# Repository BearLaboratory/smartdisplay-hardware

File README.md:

<h1 align="center" style="font-size:50px;font-weight:bold">SmartDisplay-Hardware</h1>
<p align="center">墨水屏个人显示终端硬件</p>
<p align="center">

</p>

## 描述

smartdisplay硬件基于ESP32及2.9寸墨水屏，拥有WiFi及蓝牙BLE功能。

可通过WiFi连接网络请求相关数据，同时可以通过蓝牙控制系统。

## 硬件设计

## BUG

+ 充电芯片TP4054充电功率过小
> 充电功率TP4054只有500ma,导致边冲边放无法更好给电池充电。

+ 无时钟芯片
> 无时钟芯片导致时间不准确

## 固件及APP

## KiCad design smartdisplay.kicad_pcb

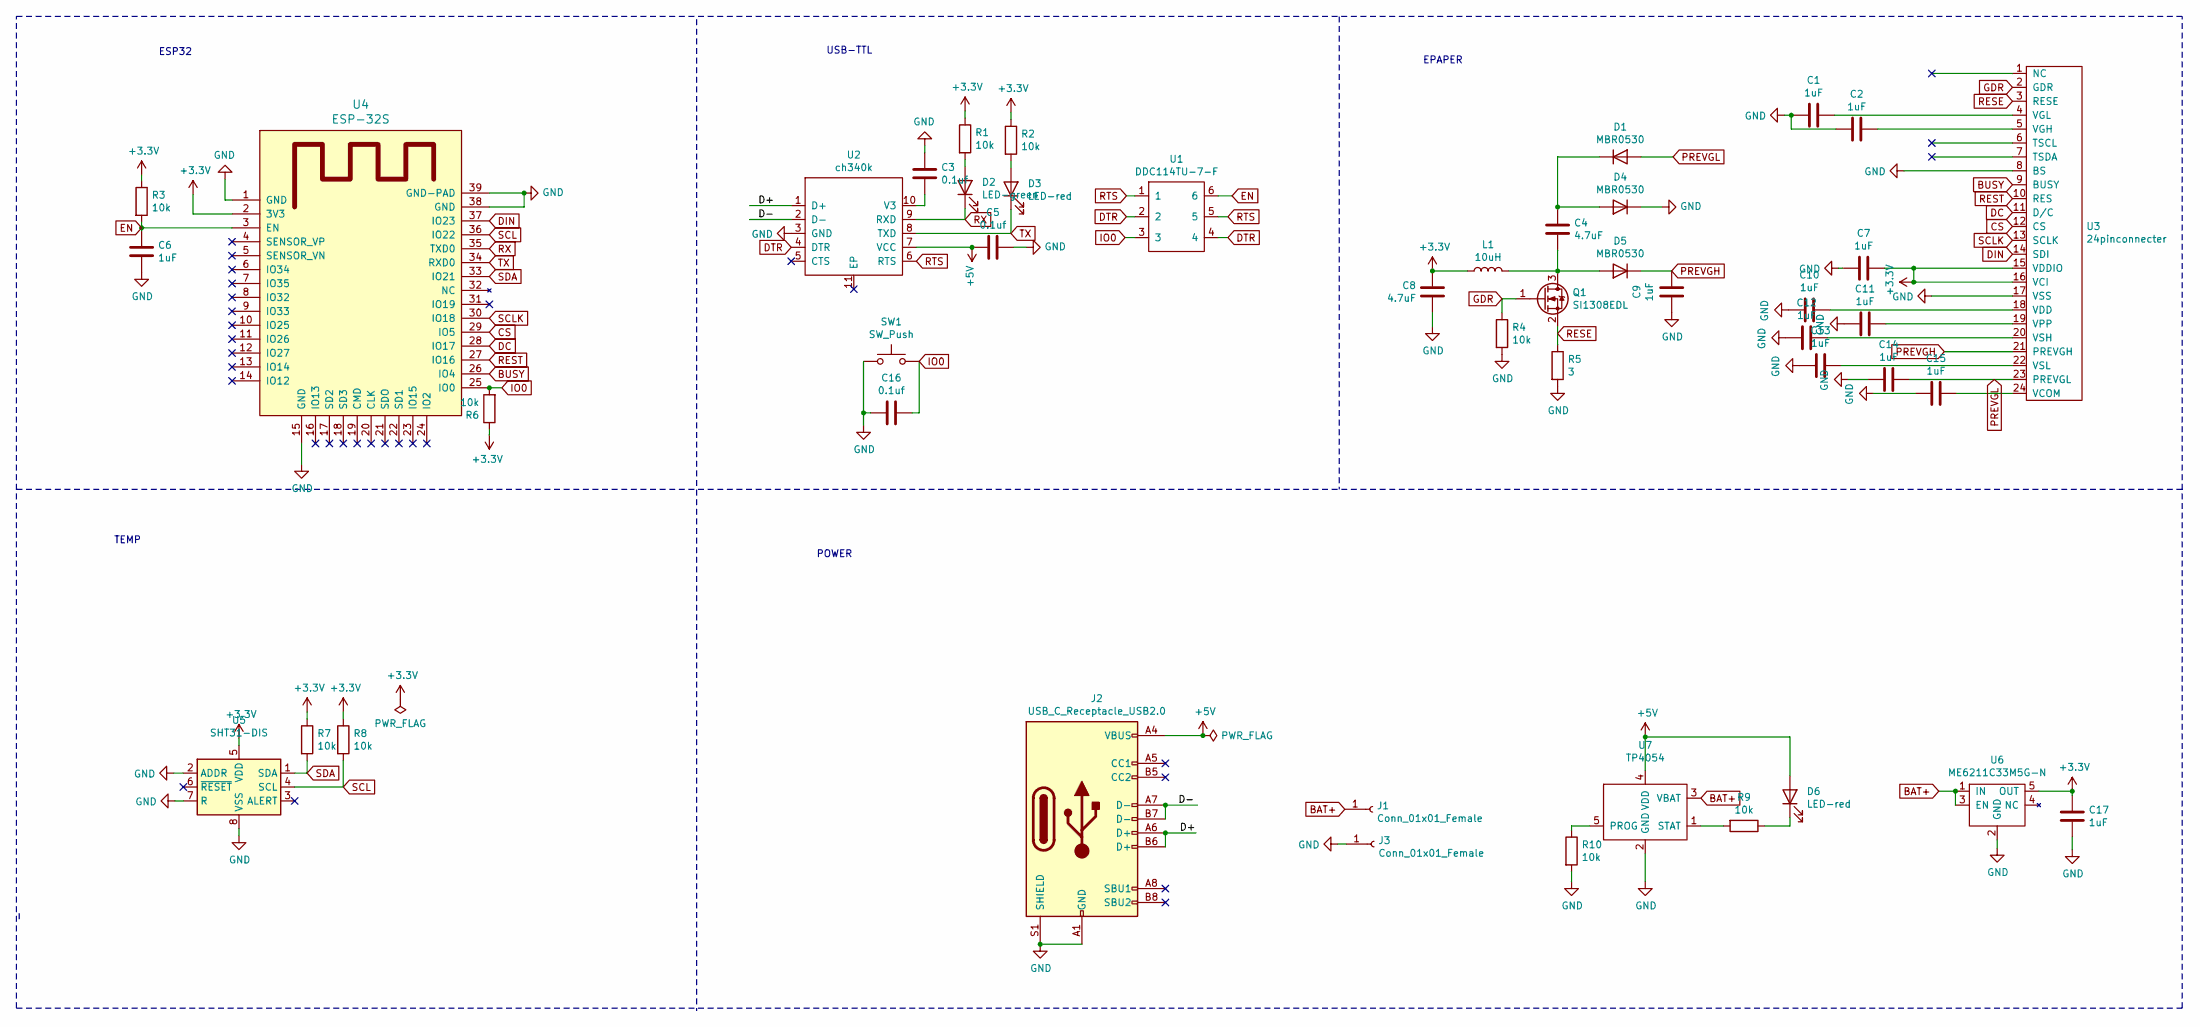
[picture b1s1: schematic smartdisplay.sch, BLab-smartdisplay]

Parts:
C1, C2, C6, C7, C9, C10, C11, C12, C13, C14, C15, C17: 1uF; C_0603_1608Metric
C3, C5, C16: 0.1uf; C_0603_1608Metric
C4, C8: 4.7uF; C_0603_1608Metric
D1, D4, D5: MBR0530; D_SOD-123
D2: LED-green; D_0603_1608Metric
D3, D6: LED-red; D_0603_1608Metric
J1, J3: Conn_01x01_Female; largepoint
J2: USB_C_Receptacle_USB2.0; USB_C_Receptacle_HRO_TYPE-C-31-M-12
L1: 10uH; L_Coilcraft_XxL4040
Q1: SI1308EDL; SOT-23
R1, R2, R3, R4, R6, R7, R8, R9, R10: 10k; R_0603_1608Metric
R5: 3; R_0603_1608Metric
SW1: SW_Push; bt-342
U1: DDC114TU-7-F; SOT-363_SC-70-6
U2: ch340k; ESSOP-10_3.9x4.9mm_P1.00mm
U3: 24pinconnecter; epd-24pin
U4: ESP-32S; ESP32-WROOM-32
U5: SHT31-DIS; Sensirion_DFN-8-1EP_2.5x2.5mm_P0.5mm_EP1.1x1.7mm
U6: ME6211C33M5G-N; SOT-23-5
U7: TP4054; SOT-23-5

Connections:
+3V3: C7.1, C8.2, C17.1, L1.1, R1.1, R2.1, R3.1, R6.1, R7.1, R8.1, U3.15 (VDDIO), U3.16 (VCI), U4.2 (3V3), U5.5 (VDD), U6.5 (OUT)
+5V: C5.1, D6.2 (A), J2.A4 (VBUS), J2.A9 (VBUS), J2.B4 (VBUS), J2.B9 (VBUS), U2.7 (VCC), U7.4 (VDD)
/D+: J2.A6 (D+), J2.B6 (D+), U2.1 (D+)
/D-: J2.A7 (D-), J2.B7 (D-), U2.2 (D-)
BAT+: J1.1, U6.1 (IN), U6.3 (EN), U7.3 (VBAT)
BUSY: U3.9 (BUSY), U4.26 (IO4)
CS: U3.12 (CS), U4.29 (IO5)
DC: U3.11 (D/C), U4.28 (IO17)
DIN: U3.14 (SDI), U4.37 (IO23)
DTR: U1.2, U1.4, U2.4 (DTR)
EN: C6.1, R3.2, U1.6, U4.3 (EN)
GDR: Q1.1 (G), R4.1, U3.2 (GDR)
GND: C1.2, C2.2, C3.1, C5.2, C6.2, C7.2, C8.1, C9.2, C10.2, C11.2, C12.2, C13.2, C14.2, C15.2, C16.1, C17.2, D4.1 (K), J2.A1 (GND), J2.A12 (GND), J2.B1 (GND), J2.B12 (GND), J2.S1 (SHIELD), J3.1, R4.2, R5.2, R10.2, SW1.1, U2.3 (GND), U3.8 (BS), U3.17 (VSS), U4.1 (GND), U4.15 (GND), U4.38 (GND), U4.39 (GND-PAD), U5.2 (ADDR), U5.7 (R), U5.8 (VSS), U5.9 (VSS), U6.2 (GND), U7.2 (GND)
IO0: C16.2, R6.2, SW1.2, U1.3, U4.25 (IO0)
unnamed: C1.1, U3.4 (VGL)
unnamed: C2.1, U3.5 (VGH)
unnamed: C3.2, U2.10 (V3)
unnamed: C4.1, D1.1 (K), D4.2 (A)
unnamed: C4.2, D5.2 (A), L1.2, Q1.3 (D)
unnamed: C10.1, U3.18 (VDD)
unnamed: C11.1, U3.19 (VPP)
unnamed: C12.1, U3.20 (VSH)
unnamed: C13.1, U3.22 (VSL)
unnamed: C15.1, U3.24 (VCOM)
unnamed: D2.2 (A), R1.2
unnamed: D3.2 (A), R2.2
unnamed: D6.1 (K), R9.1
unnamed: R9.2, U7.1 (STAT)
unnamed: R10.1, U7.5 (PROG)
PREVGH: C9.1, D5.1 (K), U3.21 (PREVGH)
PREVGL: C14.1, D1.2 (A), U3.23 (PREVGL)
RESE: Q1.2 (S), R5.1, U3.3 (RESE)
REST: U3.10 (RES), U4.27 (IO16)
RTS: U1.1, U1.5, U2.6 (RTS)
RX: D2.1 (K), U2.9 (RXD), U4.35 (TXD0)
SCL: R8.2, U4.36 (IO22), U5.4 (SCL)
SCLK: U3.13 (SCLK), U4.30 (IO18)
SDA: R7.2, U4.33 (IO21), U5.1 (SDA)
TX: D3.1 (K), U2.8 (TXD), U4.34 (RXD0)

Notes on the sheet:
ESP32
USB-TTL
EPAPER
TEMP
POWER

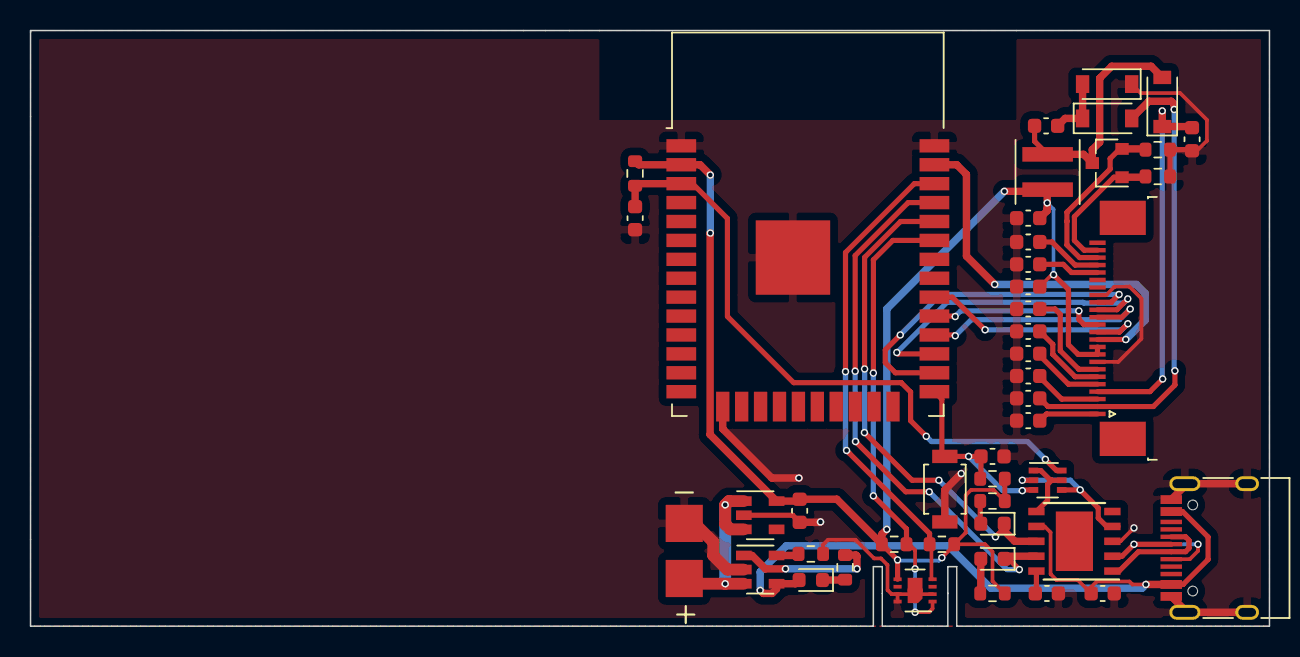
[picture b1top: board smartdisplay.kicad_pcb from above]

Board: 2 copper layers, 83.2 x 40.0 mm, 46 parts (0 on the bottom side), 39 nets.

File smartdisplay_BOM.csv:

"Comment","Description","Designator","Footprint","LibRef","Pins","Quantity","PartNumber","url",
"0.1uf","desc","C5,C16,C3,","C_0603_1608Metric","libref","2","3","","",
"4.7uF","desc","C8,C4,","C_0603_1608Metric","libref","2","2","","",
"1uF","desc","C9,C15,C14,C13,C12,C11,C10,C7,C2,C1,C17,C6,","C_0603_1608Metric","libref","2","12","","",
"LED-green","desc","D2,","D_0603_1608Metric","libref","2","1","","",
"MBR0530","desc","D5,D1,D4,","D_SOD-123","libref","2","3","","",
"LED-red","desc","D6,D3,","D_0603_1608Metric","libref","2","2","","",
"Conn_01x01_Female","desc","J3,J1,","largepoint","libref","1","2","","",
"10uH","desc","L1,","L_Coilcraft_XxL4040","libref","2","1","","",
"SI1308EDL","desc","Q1,","SOT-23","libref","3","1","","",
"10k","desc","R4,R8,R7,R6,R9,R10,R2,R1,R3,","R_0603_1608Metric","libref","2","9","","",
"3","desc","R5,","R_0603_1608Metric","libref","2","1","","",
"SW_Push","desc","SW1,","bt-342","libref","2","1","","",
"DDC114TU-7-F","desc","U1,","SOT-363_SC-70-6","libref","6","1","","",
"ch340k","desc","U2,","ESSOP-10_3.9x4.9mm_P1.00mm","libref","11","1","","",
"24pinconnecter","desc","U3,","epd-24pin","libref","26","1","","",
"ESP-32S","desc","U4,","ESP32-WROOM-32","libref","39","1","","",
"SHT31-DIS","desc","U5,","Sensirion_DFN-8-1EP_2.5x2.5mm_P0.5mm_EP1.1x1.7mm","libref","10","1","","",
"ME6211C33M5G-N","desc","U6,","SOT-23-5","libref","5","1","","",
"TP4054","desc","U7,","SOT-23-5","libref","5","1","","",
"Through Hole Items ",
"USB_C_Receptacle_USB2.0","desc","J2,","USB_C_Receptacle_HRO_TYPE-C-31-M-12","libref","22","1","","",

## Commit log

2020-02-29 init commit
2020-02-29 Create LICENSE
2020-02-29 修改readme
2020-03-01 新增外壳freecad设计
2020-03-01 修改外壳前盖设计
2021-08-24 finish v1.0

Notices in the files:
README.md:
GPL License
